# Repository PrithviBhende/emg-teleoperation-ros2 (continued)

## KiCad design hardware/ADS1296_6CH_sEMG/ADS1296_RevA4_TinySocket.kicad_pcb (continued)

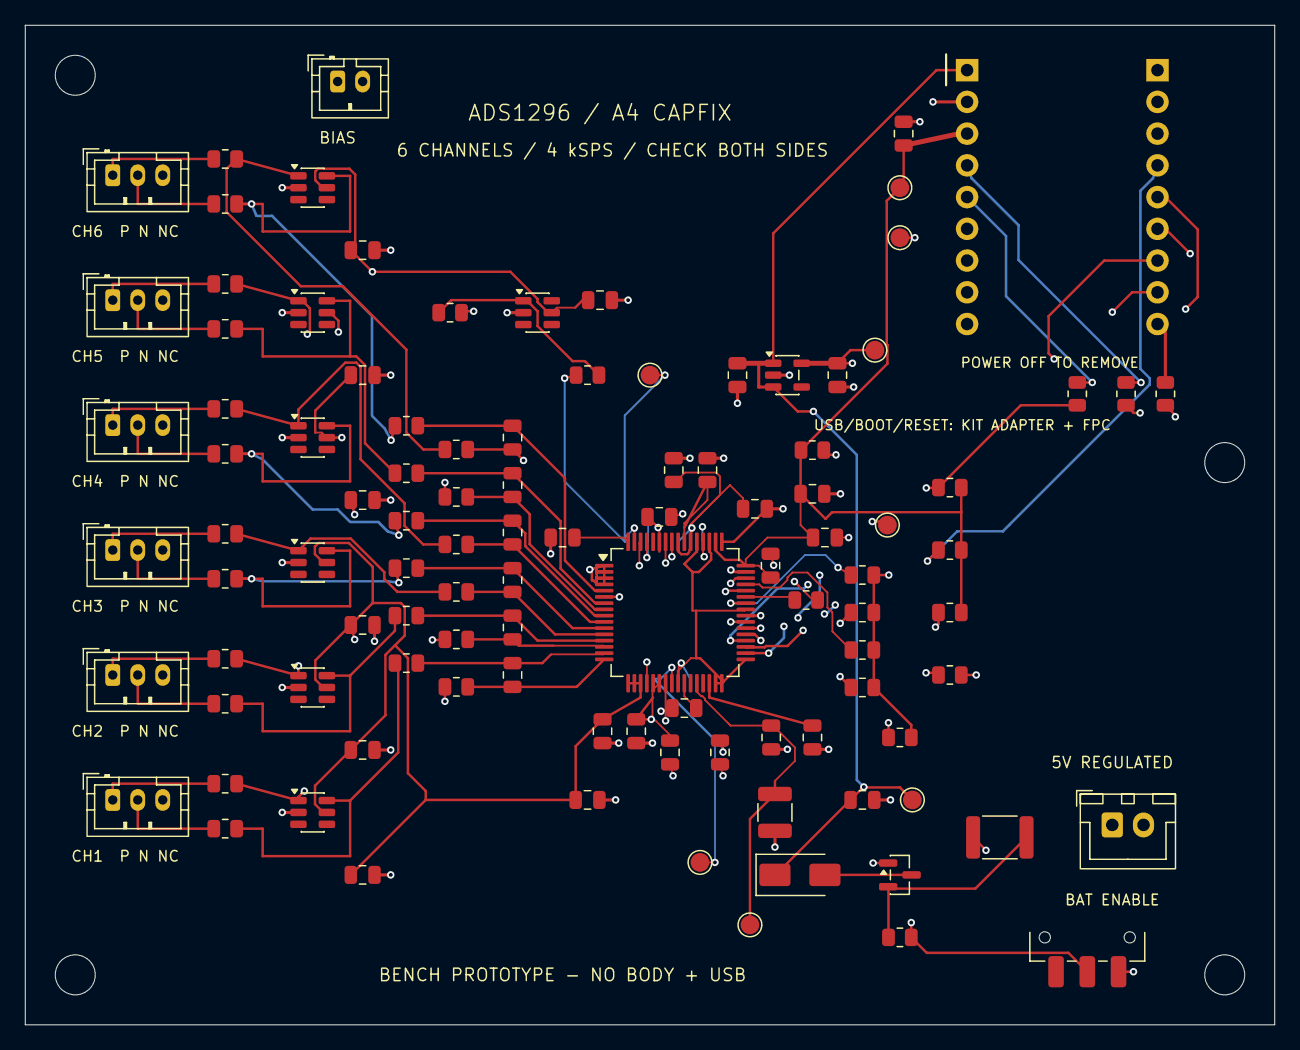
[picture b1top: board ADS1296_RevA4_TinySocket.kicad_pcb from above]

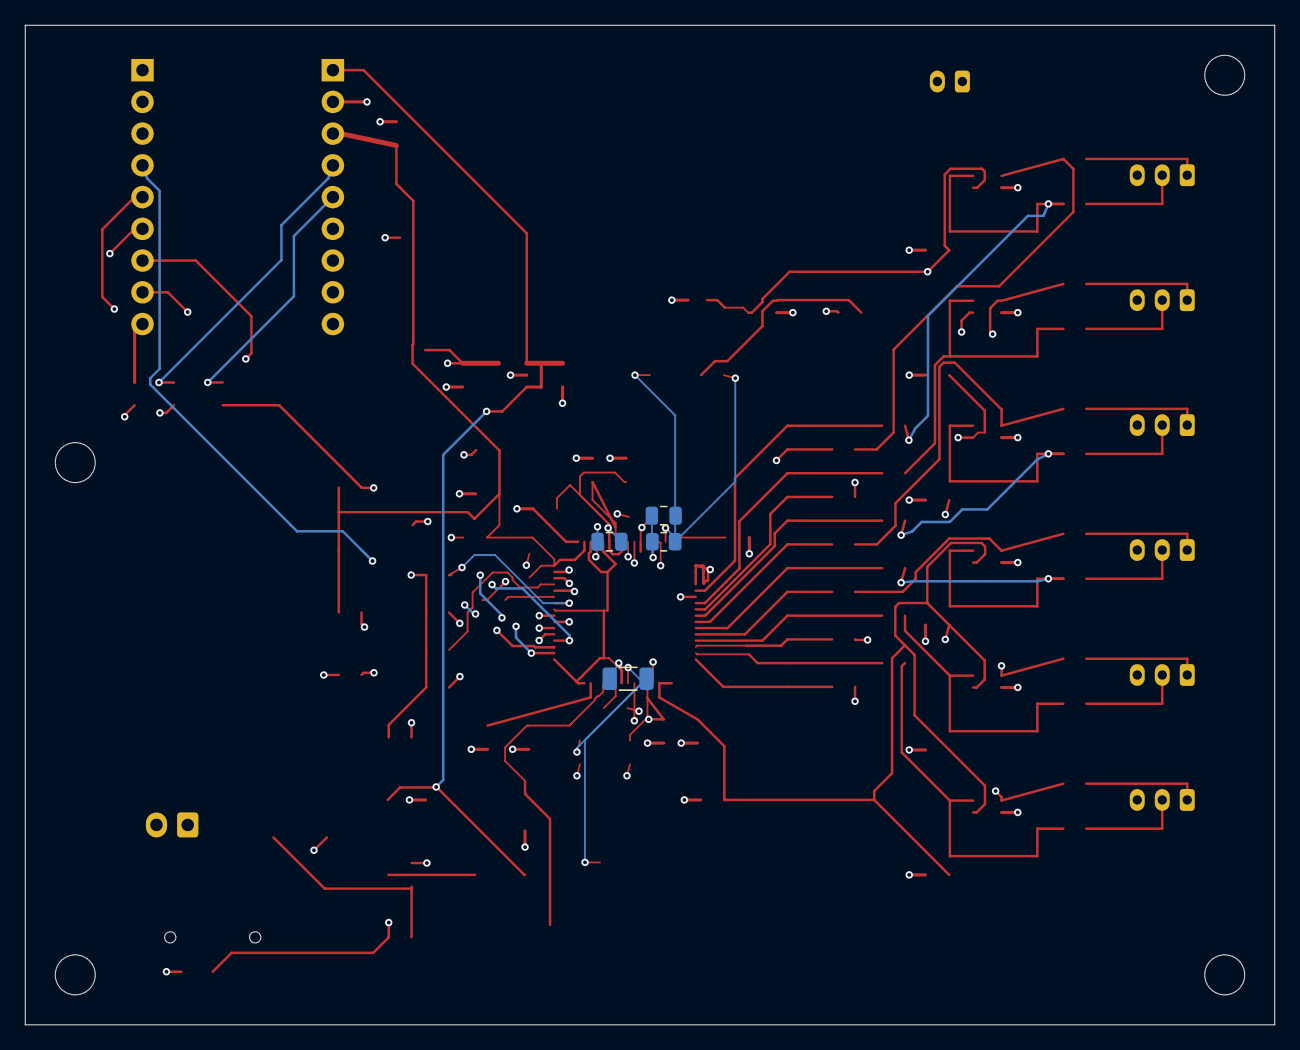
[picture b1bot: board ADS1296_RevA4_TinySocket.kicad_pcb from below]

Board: 4 copper layers, 100.0 x 80.0 mm, 113 parts (4 on the bottom side), 72 nets.

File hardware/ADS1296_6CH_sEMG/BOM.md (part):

# A4S Tiny carrier CapFix - complete BOM

C14, C27, R21 and C23 mount on B.Cu (underside); all other carrier components mount on F.Cu (top). Plan for two-sided assembly. Resistors/capacitors remain 0805 or larger. U1 still requires 0.5mm-pitch soldering. Component values and packages are unchanged from A4; refer to both assembly drawings for positions.

|Ref|Value / exact MPN|Footprint|Purpose / electrical rating|Source|
|---|---|---|---|---|
|J1|REGULATED 5V IN / B2B-XH-A(LF)(SN)|Connector_JST:JST_XH_B2B-XH-A_1x02_P2.50mm_Vertical|5.0-5.25V regulated source, not raw Li-ion; use battery OR USB for initial tests|[Manufacturer](https://www.jst-mfg.com/product/pdf/eng/eXH.pdf)|
|F1|750mA PTC / MF-MSMF075-2|Fuse:Fuse_1812_4532Metric|0.75A hold / 1.5A trip,13.2V; battery branch only|[Manufacturer](https://www.bourns.com/docs/product-datasheets/mfmsmf.pdf)|
|SW1|BATTERY ENABLE / JS102011SAQN|Button_Switch_SMD:SW_SPDT_CK_JS102011SAQN|SPDT switches MOSFET gate only; USB stays powered with switch OFF|[Manufacturer](https://www.ckswitches.com/media/1422/js.pdf)|
|Q1|AO3401A / AO3401A|Package_TO_SOT_SMD:SOT-23|S=2, D=3, G=1; P-channel battery high-side switch|[Manufacturer](https://www.aosmd.com/pdfs/datasheet/AO3401A.pdf)|
|R47|100k / RC0805FR-07100KL|Resistor_SMD:R_0805_2012Metric|100k; 1%; 0805; 0.125W; >=50V; Default battery OFF|[Manufacturer](https://www.yageogroup.com/content/datasheet/asset/file/PYU-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|
|D1|SS14 / SS14|Diode_SMD:D_SMA|Cathode1=VSYS,anode2=BAT_SWITCHED; blocks USB backfeed to battery|[Manufacturer](https://www.diodes.com/assets/Datasheets/ds23001.pdf)|
|C1|100n / C0805C104K4RACTU|Capacitor_SMD:C_0805_2012Metric|100n; X7R 10% 16V; Additional carrier bypass; Tiny has its own 10uF input capacitor|[Manufacturer](https://yageogroup.com/download/specsheet/C0805C104K4RACTU)|
|U2|LP5907MFX-3.3/NOPB / LP5907MFX-3.3/NOPB|Package_TO_SOT_SMD:SOT-23-5|3.3V 250mA low-noise LDO; SOT23-5; analogue supply only|[Manufacturer](https://www.ti.com/lit/ds/symlink/lp5907.pdf)|
|C2|2u2 / C0805C225K4RACTU|Capacitor_SMD:C_0805_2012Metric|2u2; X7R 10% 16V; |[Manufacturer](https://yageogroup.com/download/specsheet/C0805C225K4RACTU)|
|C3|2u2 / C0805C225K4RACTU|Capacitor_SMD:C_0805_2012Metric|2u2; X7R 10% 16V; |[Manufacturer](https://yageogroup.com/download/specsheet/C0805C225K4RACTU)|
|TP1|AVDD|TestPoint:TestPoint_Pad_D1.5mm|Analogue 3.3V test point|Mechanical|
|TP2|VSYS|TestPoint:TestPoint_Pad_D1.5mm|5V rail after source diodes|Mechanical|
|C27|1u / C0805C105K4RACTU|Capacitor_SMD:C_0805_2012Metric|1u; X7R 10% 16V; Local AVDD1 pin54 bulk|[Manufacturer](https://yageogroup.com/download/specsheet/C0805C105K4RACTU)|
|C5|100n / C0805C104K4RACTU|Capacitor_SMD:C_0805_2012Metric|100n; X7R 10% 16V; Local U1 pin 19 bypass|[Manufacturer](https://yageogroup.com/download/specsheet/C0805C104K4RACTU)|
|C6|100n / C0805C104K4RACTU|Capacitor_SMD:C_0805_2012Metric|100n; X7R 10% 16V; Local U1 pin 21 bypass|[Manufacturer](https://yageogroup.com/download/specsheet/C0805C104K4RACTU)|
|C7|100n / C0805C104K4RACTU|Capacitor_SMD:C_0805_2012Metric|100n; X7R 10% 16V; Local U1 pin 22 bypass|[Manufacturer](https://yageogroup.com/download/specsheet/C0805C104K4RACTU)|
|C8|100n / C0805C104K4RACTU|Capacitor_SMD:C_0805_2012Metric|100n; X7R 10% 16V; Local U1 pin 54 bypass|[Manufacturer](https://yageogroup.com/download/specsheet/C0805C104K4RACTU)|
|C9|100n / C0805C104K4RACTU|Capacitor_SMD:C_0805_2012Metric|100n; X7R 10% 16V; Local U1 pin 56 bypass|[Manufacturer](https://yageogroup.com/download/specsheet/C0805C104K4RACTU)|
|C10|100n / C0805C104K4RACTU|Capacitor_SMD:C_0805_2012Metric|100n; X7R 10% 16V; Local U1 pin 59 bypass|[Manufacturer](https://yageogroup.com/download/specsheet/C0805C104K4RACTU)|
|C11|1u / C0805C105K4RACTU|Capacitor_SMD:C_0805_2012Metric|1u; X7R 10% 16V; |[Manufacturer](https://yageogroup.com/download/specsheet/C0805C105K4RACTU)|
|C12|100n / C0805C104K4RACTU|Capacitor_SMD:C_0805_2012Metric|100n; X7R 10% 16V; U1 pin48 bypass|[Manufacturer](https://yageogroup.com/download/specsheet/C0805C104K4RACTU)|
|C13|100n / C0805C104K4RACTU|Capacitor_SMD:C_0805_2012Metric|100n; X7R 10% 16V; U1 pin50 bypass|[Manufacturer](https://yageogroup.com/download/specsheet/C0805C104K4RACTU)|
|U1|ADS1296IPAG / ADS1296IPAG|Package_QFP:TQFP-64_10x10mm_P0.5mm|All 64 pins transcribed from TI SBAS459K pp10-11; non-respiration 6-channel version|[Manufacturer](https://www.ti.com/lit/ds/symlink/ads1298.pdf)|
|C14|10u / C1206C106K4PACTU|Capacitor_SMD:C_1206_3216Metric|10u; X5R 10% 16V; |[Manufacturer](https://yageogroup.com/download/specsheet/C1206C106K4PACTU)|
|C15|100n / C0805C104K4RACTU|Capacitor_SMD:C_0805_2012Metric|100n; X7R 10% 16V; |[Manufacturer](https://yageogroup.com/download/specsheet/C0805C104K4RACTU)|
|C16|22u / C1210C226K4PACTU|Capacitor_SMD:C_1210_3225Metric|22u; X5R 10% 16V; |[Manufacturer](https://yageogroup.com/download/specsheet/C1210C226K4PACTU)|
|C17|100n / C0805C104K4RACTU|Capacitor_SMD:C_0805_2012Metric|100n; X7R 10% 16V; |[Manufacturer](https://yageogroup.com/download/specsheet/C0805C104K4RACTU)|
|C18|1u / C0805C105K4RACTU|Capacitor_SMD:C_0805_2012Metric|1u; X7R 10% 16V; |[Manufacturer](https://yageogroup.com/download/specsheet/C0805C105K4RACTU)|
|C19|1u / C0805C105K4RACTU|Capacitor_SMD:C_0805_2012Metric|1u; X7R 10% 16V; |[Manufacturer](https://yageogroup.com/download/specsheet/C0805C105K4RACTU)|
|C20|1u / C0805C105K4RACTU|Capacitor_SMD:C_0805_2012Metric|1u; X7R 10% 16V; |[Manufacturer](https://yageogroup.com/download/specsheet/C0805C105K4RACTU)|
|C21|1n / C0805C102J5GACTU|Capacitor_SMD:C_0805_2012Metric|1n; C0G 5% 50V; |[Manufacturer](https://yageogroup.com/download/specsheet/C0805C102J5GACTU)|
|C22|1u / C0805C105K4RACTU|Capacitor_SMD:C_0805_2012Metric|1u; X7R 10% 16V; |[Manufacturer](https://yageogroup.com/download/specsheet/C0805C105K4RACTU)|
|R10|10k / RC0805FR-0710KL|Resistor_SMD:R_0805_2012Metric|10k; 1%; 0805; 0.125W; >=50V; Unused ADS GPIO pulldown; leave configured as input|[Manufacturer](https://www.yageogroup.com/content/datasheet/asset/file/PYU-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|
|R11|10k / RC0805FR-0710KL|Resistor_SMD:R_0805_2012Metric|10k; 1%; 0805; 0.125W; >=50V; Unused ADS GPIO pulldown; leave configured as input|[Manufacturer](https://www.yageogroup.com/content/datasheet/asset/file/PYU-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|
|R12|10k / RC0805FR-0710KL|Resistor_SMD:R_0805_2012Metric|10k; 1%; 0805; 0.125W; >=50V; Unused ADS GPIO pulldown; leave configured as input|[Manufacturer](https://www.yageogroup.com/content/datasheet/asset/file/PYU-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|
|R13|10k / RC0805FR-0710KL|Resistor_SMD:R_0805_2012Metric|10k; 1%; 0805; 0.125W; >=50V; Unused ADS GPIO pulldown; leave configured as input|[Manufacturer](https://www.yageogroup.com/content/datasheet/asset/file/PYU-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|
|R14|10k / RC0805FR-0710KL|Resistor_SMD:R_0805_2012Metric|10k; 1%; 0805; 0.125W; >=50V; |[Manufacturer](https://www.yageogroup.com/content/datasheet/asset/file/PYU-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|
|R15|10k / RC0805FR-0710KL|Resistor_SMD:R_0805_2012Metric|10k; 1%; 0805; 0.125W; >=50V; 10k pulldown; optional clock output remains disabled|[Manufacturer](https://www.yageogroup.com/content/datasheet/asset/file/PYU-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|
|TP3|VREFP|TestPoint:TestPoint_Pad_D1.5mm|Bench test point; use high impedance probe|Mechanical|
|TP4|VCAP1|TestPoint:TestPoint_Pad_D1.5mm|Bench test point; use high impedance probe|Mechanical|
|TP5|ADS_DRDY_N|TestPoint:TestPoint_Pad_D1.5mm|Bench test point; use high impedance probe|Mechanical|
|J2|CH1: P / N / SHIELD / B3B-PH-K-S(LF)(SN)|Connector_JST:JST_PH_B3B-PH-K_1x03_P2.00mm_Vertical|JST PH 3-pin; pin1 positive electrode, pin2 negative electrode, pin3 shield (NC A4S)|[Manufacturer](https://www.jst-mfg.com/product/pdf/eng/ePH.pdf)|
|R111|22k / RT0805BRD0722KL|Resistor_SMD:R_0805_2012Metric|22k; 0.1%, <=25 ppm/K; 0805; 0.125W; >=50V; |[Manufacturer](https://yageogroup.com/content/datasheet/asset/file/pyu-rt_1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|
|R112|22k / RT0805BRD0722KL|Resistor_SMD:R_0805_2012Metric|22k; 0.1%, <=25 ppm/K; 0805; 0.125W; >=50V; |[Manufacturer](https://yageogroup.com/content/datasheet/asset/file/pyu-rt_1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|
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
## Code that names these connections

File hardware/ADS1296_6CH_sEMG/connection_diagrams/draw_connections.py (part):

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    d.text(350,yn+37,f'{u} protection connects at the dots → picture 03',18,MUTED)
    d.text(70,yn+25,'pin 3: NC',18,MUTED)
d.text(1460,245,'2  Digital wires (SPI + control)',28,bold=True)
spi=[('CS_N',39,5,'GPIO2','R33'),('SCLK',40,18,'GPIO12','R31'),
     ('DIN / MOSI',34,4,'GPIO1','R32'),('DOUT / MISO',43,17,'GPIO13','R34'),
     ('DRDY_N',47,16,'GPIO14',None),('START',38,15,'GPIO15',None),
     ('PWDN_N',35,14,'GPIO16',None),('RESET_N',36,13,'GPIO17',None)]
for i,(sig,up,ap,gpio,r) in enumerate(spi):
    y=500+i*92
    d.text(1322,y-13,f'{up}  {sig}',19,anchor='end')
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d.panel(40,745,1135,605,'2  Supply capacitors: each branch goes to GND')
bank(65,815,1085,'VSYS input bypass','VSYS','GND',['C1','C2'])
bank(65,958,1085,'Analog rail local bypass','AVDD','GND',['C5','C6','C7','C8','C9','C10'])
bank(65,1101,1085,'Analog bulk + pin 54 local branch','AVDD','GND',['C11','C27'])
d.text(80,1290,'C3 is drawn at U2 above. Each protection IC also has 100 nF.',20,MUTED)
d.panel(1210,745,1145,605,'3  Internal reference and internal regulator capacitors')
rows=[('24  VREFP',['C14','C15'],24),('28  VCAP1',['C16','C17'],28),('30  VCAP2',['C18'],30),('55  VCAP3',['C19'],55),('26  VCAP4',['C20'],26),('64  WCT',['C21'],64)]
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    for r in refs:same(('U1',pin),(r,1))
d.text(1240,1320,'U1 pin 25 (VREFN) → GND. ∥ means parallel components.',20,MUTED)
d.panel(40,1385,1135,690,'4  ADS1296 supply pins and digital bypass')
d.text(75,1470,'AVDD → U1 pins 19, 21, 22, 54, 56, 59',25,RED,bold=True)
d.text(75,1520,'3V3_D → U1 pins 48, 50',25,RED,bold=True)
d.text(75,1570,'GND → U1 pins 20, 23, 25, 32, 33, 49, 51, 53, 57, 58',22,MUTED)
bank(65,1610,1085,'Digital rail bypass','3V3_D','GND',['C12','C13','C22','C26'])
d.text(75,1800,'Other fixed U1 connections',25,bold=True)
d.text(75,1850,'AVDD → pins 1, 2, 3, 4, 17, 18, 62',23,RED)
d.text(75,1895,'GND → pins 31 and 41',23,MUTED)
d.text(75,1940,'NC → pins 27, 29 and 60',23,MUTED)
d.text(75,2000,'Pin 60 uses the internal RLD reference in this design.',20,MUTED)
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    terminal=2 if r=='R14' else 1
    same(('U1',pin),(r,terminal))
    same((r,3-terminal),('A1',3 if rail=='3V3_D' else 2))
for rail,pins in [('AVDD',[1,2,3,4,17,18,19,21,22,54,56,59,62]),('3V3_D',[48,50]),('GND',[20,23,25,31,32,33,41,49,51,53,57,58])]:
    for p in pins:assert net('U1',p)==rail
for refs,rail in [(['C1','C2'],'VSYS'),(['C3','C5','C6','C7','C8','C9','C10','C11','C27'],'AVDD'),(['C12','C13','C22','C26'],'3V3_D')]:
    for r in refs:assert net(r,1)==rail
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d.text(875,400,'U3 · TPD4E001',26,bold=True,anchor='middle')
d.text(685,437,'pin 1 IO1',21);d.text(685,470,'pin 6 IO4',21)
d.wire([(730,285),(730,360)]);d.wire([(730,485),(730,555)])
d.text(1120,403,'pin 5 VCC → AVDD',22,RED)
d.text(1120,447,'pin 2 GND → GND',22,MUTED)
d.text(1120,487,'pins 3 + 4 → NC',21,MUTED)
d.cap(1850,285,555,'C111  1.8 nF')
d.text(80,660,'J2 pin 3: NC',23,MUTED)
d.text(80,712,'C112 100 nF: U3 pin 5 (AVDD) → capacitor → U3 pin 2 (GND)',24)
d.text(80,757,'The differential capacitor bridges IN1P and IN1N. It does not connect to GND.',22,MUTED)
d.panel(40,830,2315,405,'2  Repeat the same circuit for all six channels')
headers=[(75,'Channel / jack'),(380,'22 kΩ pair'),(730,'Protection IC'),(1080,'24.9 kΩ pair'),(1450,'1.8 nF bridge'),(1820,'100 nF bypass'),(2150,'U1 P / N')]
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    u=f'U{ch+2}';c=f'C1{ch}2'
    same((u,5),(c,1),('U2',5));same((u,2),(c,2),('U2',2))
d.panel(40,1265,2315,510,'3  RLD feedback and J8 bias output')
d.text(75,1415,'U1 pin 63',23,bold=True);d.text(75,1450,'RLDOUT',21,GREEN)
d.wire([(230,1410),(780,1410)],GREEN);d.dot(340,1410,GREEN)
d.resistor(780,1410,'R22',170,GREEN);d.wire([(950,1410),(1350,1410)],GREEN);d.dot(1110,1410,GREEN)
d.resistor(1350,1410,'R23',170,GREEN);d.wire([(1520,1410),(2020,1410)],GREEN)
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# Horizontal capacitor for the parallel RLD branch.
d.wire([(440,1630),(495,1630)],GREEN);d.wire([(495,1614),(495,1646)],GREEN)
d.wire([(511,1614),(511,1646)],GREEN);d.wire([(511,1630),(700,1630)],GREEN);d.dot(700,1630,GREEN)
d.text(500,1685,'C23  1.5 nF',21,anchor='middle');d.text(820,1657,'U1 pin 61 RLDINV',22,bold=True)
d.box(1050,1500,390,170,'#e8f4ee','#71a288');d.wire([(1110,1410),(1110,1500)],GREEN)
d.text(1075,1540,'U9 · TPD4E001',25,bold=True);d.text(1075,1577,'pin 1: RLD_CLAMP tap',21)
d.text(1075,1613,'pin 5 → AVDD; pin 2 → GND',20);d.text(1075,1648,'pins 3, 4, 6: NC',20)
d.text(1530,1565,'C24 100 nF: AVDD → capacitor → GND',22)
d.text(1530,1610,'R21 and C23 both bridge pins 63 and 61.',22,GREEN)
d.text(1530,1660,'RLD starts disabled; this drawing shows its wiring.',20,MUTED)
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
